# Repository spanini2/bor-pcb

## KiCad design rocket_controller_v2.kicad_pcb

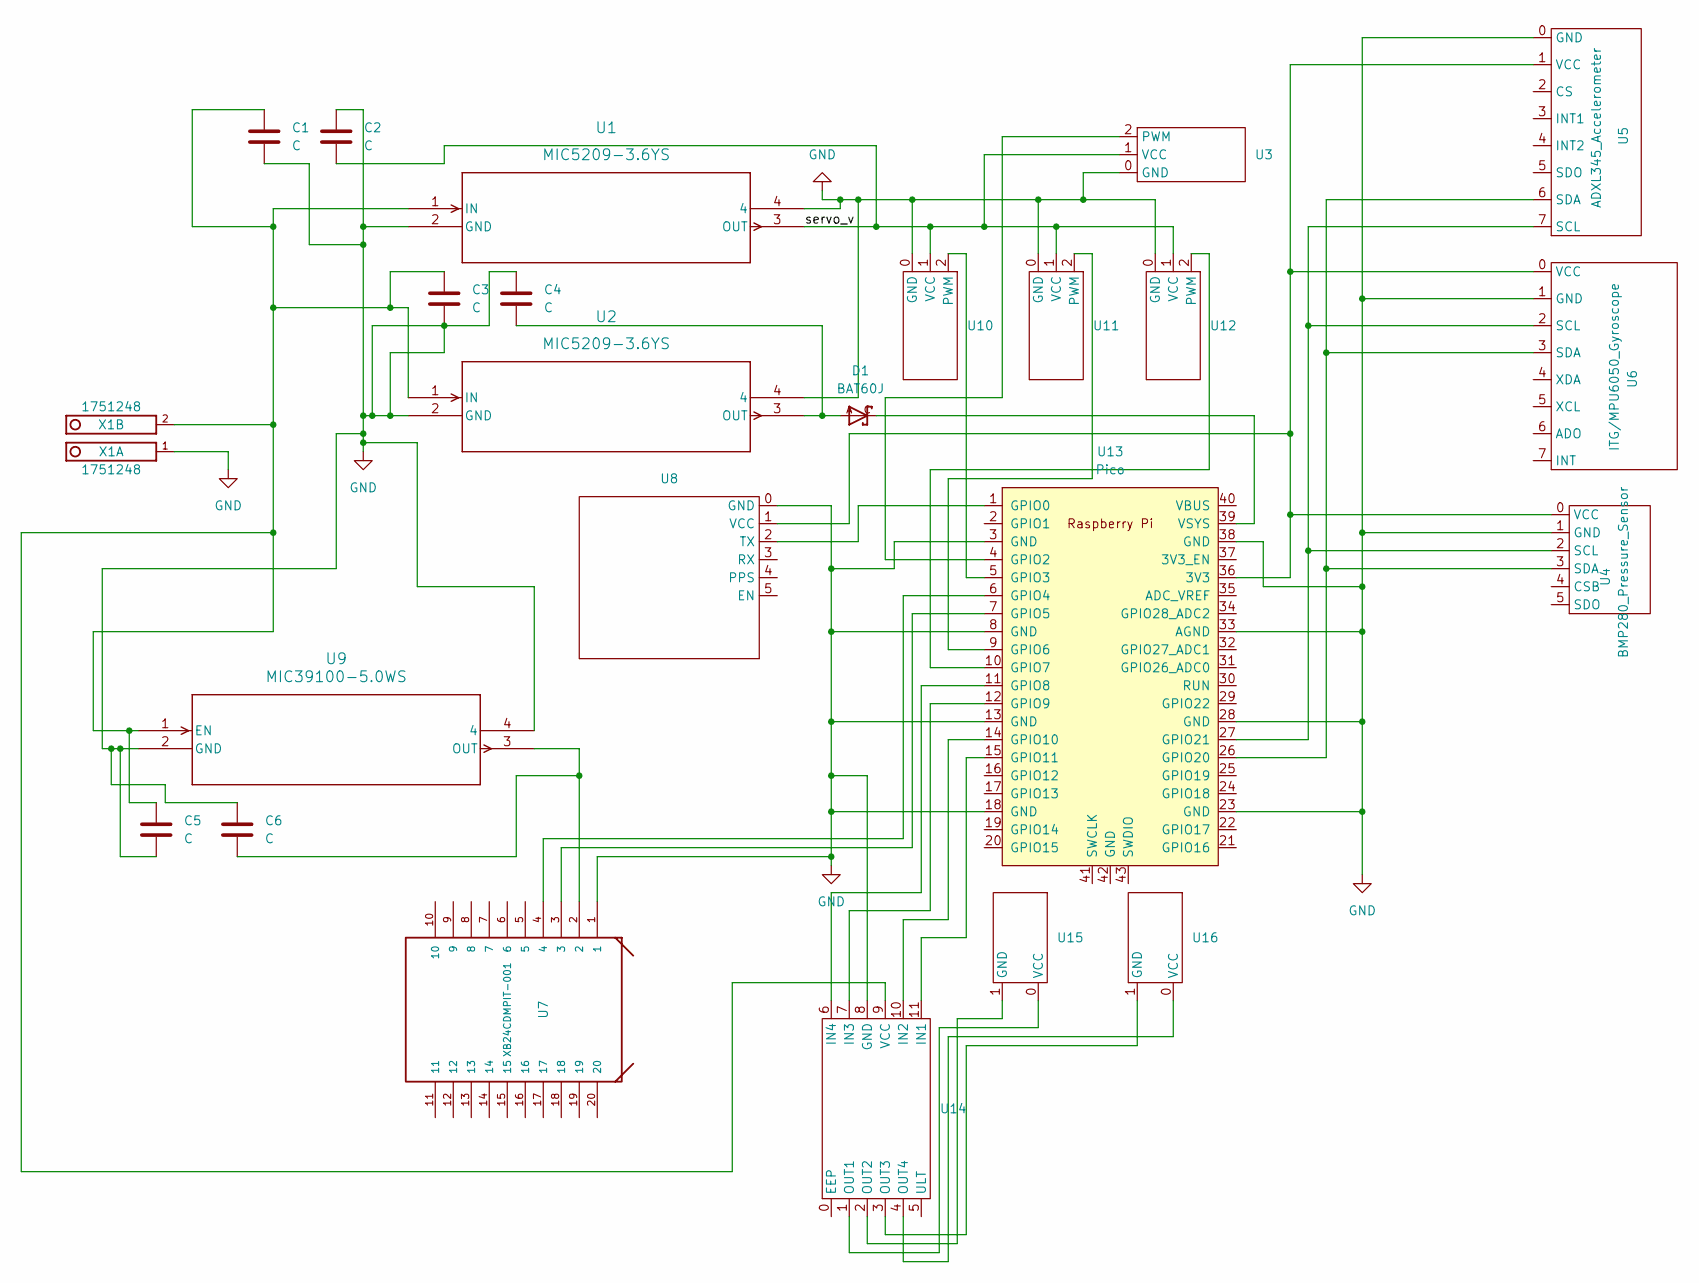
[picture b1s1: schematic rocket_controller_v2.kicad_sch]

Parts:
C1, C2, C3, C4, C5, C6: C; 0603_Capacitor
D1: BAT60J; SOD323_ST
U1, U2: MIC5209-3.6YS; MIC5209-5
U3, U10, U11, U12: Servo_Pin_Header
U4: BMP280_Pressure_Sensor
U5: ADXL345_Accelerometer
U6: ITG/MPU6050_Gyroscope; MPU6050_Gyroscope
U7: XB24CDMPIT-001; XBEE_S2C
U8: GN801_GPS
U9: MIC39100-5.0WS
U13: Pico; RPi_Pico_SMD_TH
U14: DRV8833_Motor_Driver
U15, U16: Motor_Pin_Header
X1: 1751248

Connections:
/servo_v: C2.2, U1.3 (OUT), U3.1 (VCC), U10.1 (VCC), U11.1 (VCC), U12.1 (VCC)
GND: C1.2, C2.1, C3.2, C4.1, C5.2, C6.1, U1.2 (GND), U1.4, U2.2 (GND), U2.4, U3.0 (GND), U4.1 (GND), U5.0 (GND), U6.1 (GND), U7.1, U8.0 (GND), U9.2 (GND), U9.4, U10.0 (GND), U11.0 (GND), U12.0 (GND), U13.3 (GND), U13.8 (GND), U13.13 (GND), U13.18 (GND), U13.23 (GND), U13.28 (GND), U13.33 (AGND), U13.38 (GND), U14.8 (GND), X1.1
unnamed: C1.1, C3.1, C5.1, U1.1 (IN), U2.1 (IN), U9.1 (EN), U14.9 (VCC), X1.2
unnamed: C4.2, D1.A, U2.3 (OUT)
unnamed: C6.2, U7.2, U9.3 (OUT)
unnamed: U10.2 (PWM), U13.5 (GPIO3)
unnamed: U11.2 (PWM), U13.9 (GPIO6)
unnamed: U12.2 (PWM), U13.10 (GPIO7)
unnamed: U4.0 (VCC), U5.1 (VCC), U6.0 (VCC), U8.1 (VCC), U13.36 (3V3)
unnamed: U8.2 (TX), U13.1 (GPIO0)
unnamed: U3.2 (PWM), U13.4 (GPIO2)
unnamed: U7.4, U13.6 (GPIO4)
unnamed: U7.3, U13.7 (GPIO5)
unnamed: U13.11 (GPIO8), U14.6 (IN4)
unnamed: U13.12 (GPIO9), U14.7 (IN3)
unnamed: U13.14 (GPIO10), U14.10 (IN2)
unnamed: U13.15 (GPIO11), U14.11 (IN1)
unnamed: U4.3 (SDA), U5.6 (SDA), U6.3 (SDA), U13.26 (GPIO20)
unnamed: U4.2 (SCL), U5.7 (SCL), U6.2 (SCL), U13.27 (GPIO21)
unnamed: D1.C, U13.39 (VSYS)
unnamed: U14.1 (OUT1), U15.0 (VCC)
unnamed: U14.2 (OUT2), U15.1 (GND)
unnamed: U14.3 (OUT3), U16.1 (GND)
unnamed: U14.4 (OUT4), U16.0 (VCC)

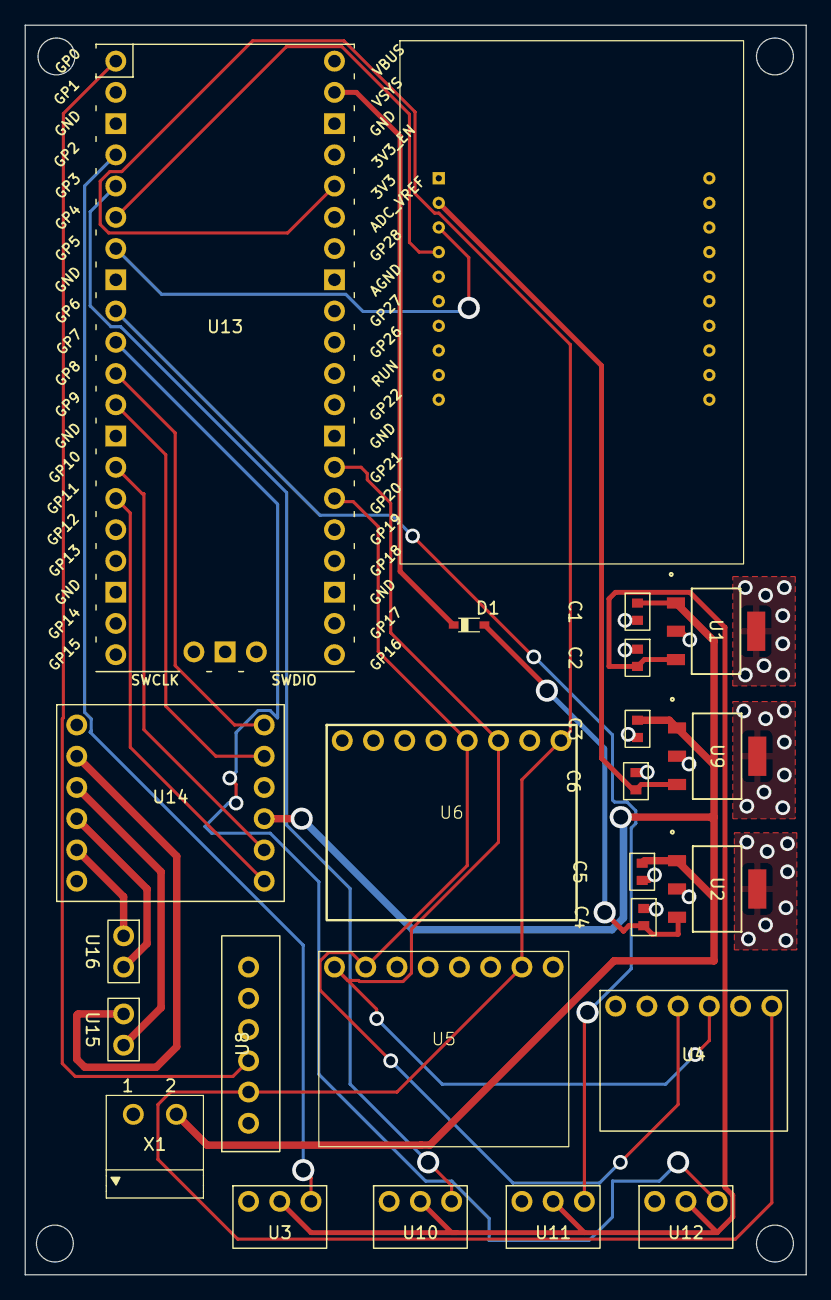
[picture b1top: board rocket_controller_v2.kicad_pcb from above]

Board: 2 copper layers, 63.5 x 101.6 mm, 24 parts (0 on the bottom side), 24 nets.

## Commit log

2024-08-30 initial
2024-08-31 added lib and updated lib paths in tables
